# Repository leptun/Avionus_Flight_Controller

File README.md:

# Avionus_Flight_Controller

This repo contains the mainboard for the Avionus project, a semi-autonomous plane/drone. The project is work in progress 🚧.

Features:
- STM32F722ZE MCU with hardware float, 512KB of flash and 256KB of RAM
- 16MB total of external dual-mode QuadSPI (QPI) flash memory with XIP capability
- Full size SD card slot
- GPS (ublox MAX-M10S) with onboard antenna
- 9dof IMU ICM-20948
- LIDAR distance sensors with headers for:
  - LIDAR07-100W
  - VL53L1X
- 16 servo outputs (including at least one UART connection)
- RC remote input:
  - PPM interface
  - iBus interface
- LoRa 868MHz module using Semtech SX1262
- USB 2.0 FS with Type C connector (device only)
- Independent power domanins for the peripherals:
  - Power domains voltage measurement and monitoring
  - Current measurement of critical power domains
  - Very low power shutdown with wake from RTC
  - ESD protection of all IO
- STDC14 debugging header for STLINK-V3:
  - SWD
  - JTAG
  - SWO
  - UART

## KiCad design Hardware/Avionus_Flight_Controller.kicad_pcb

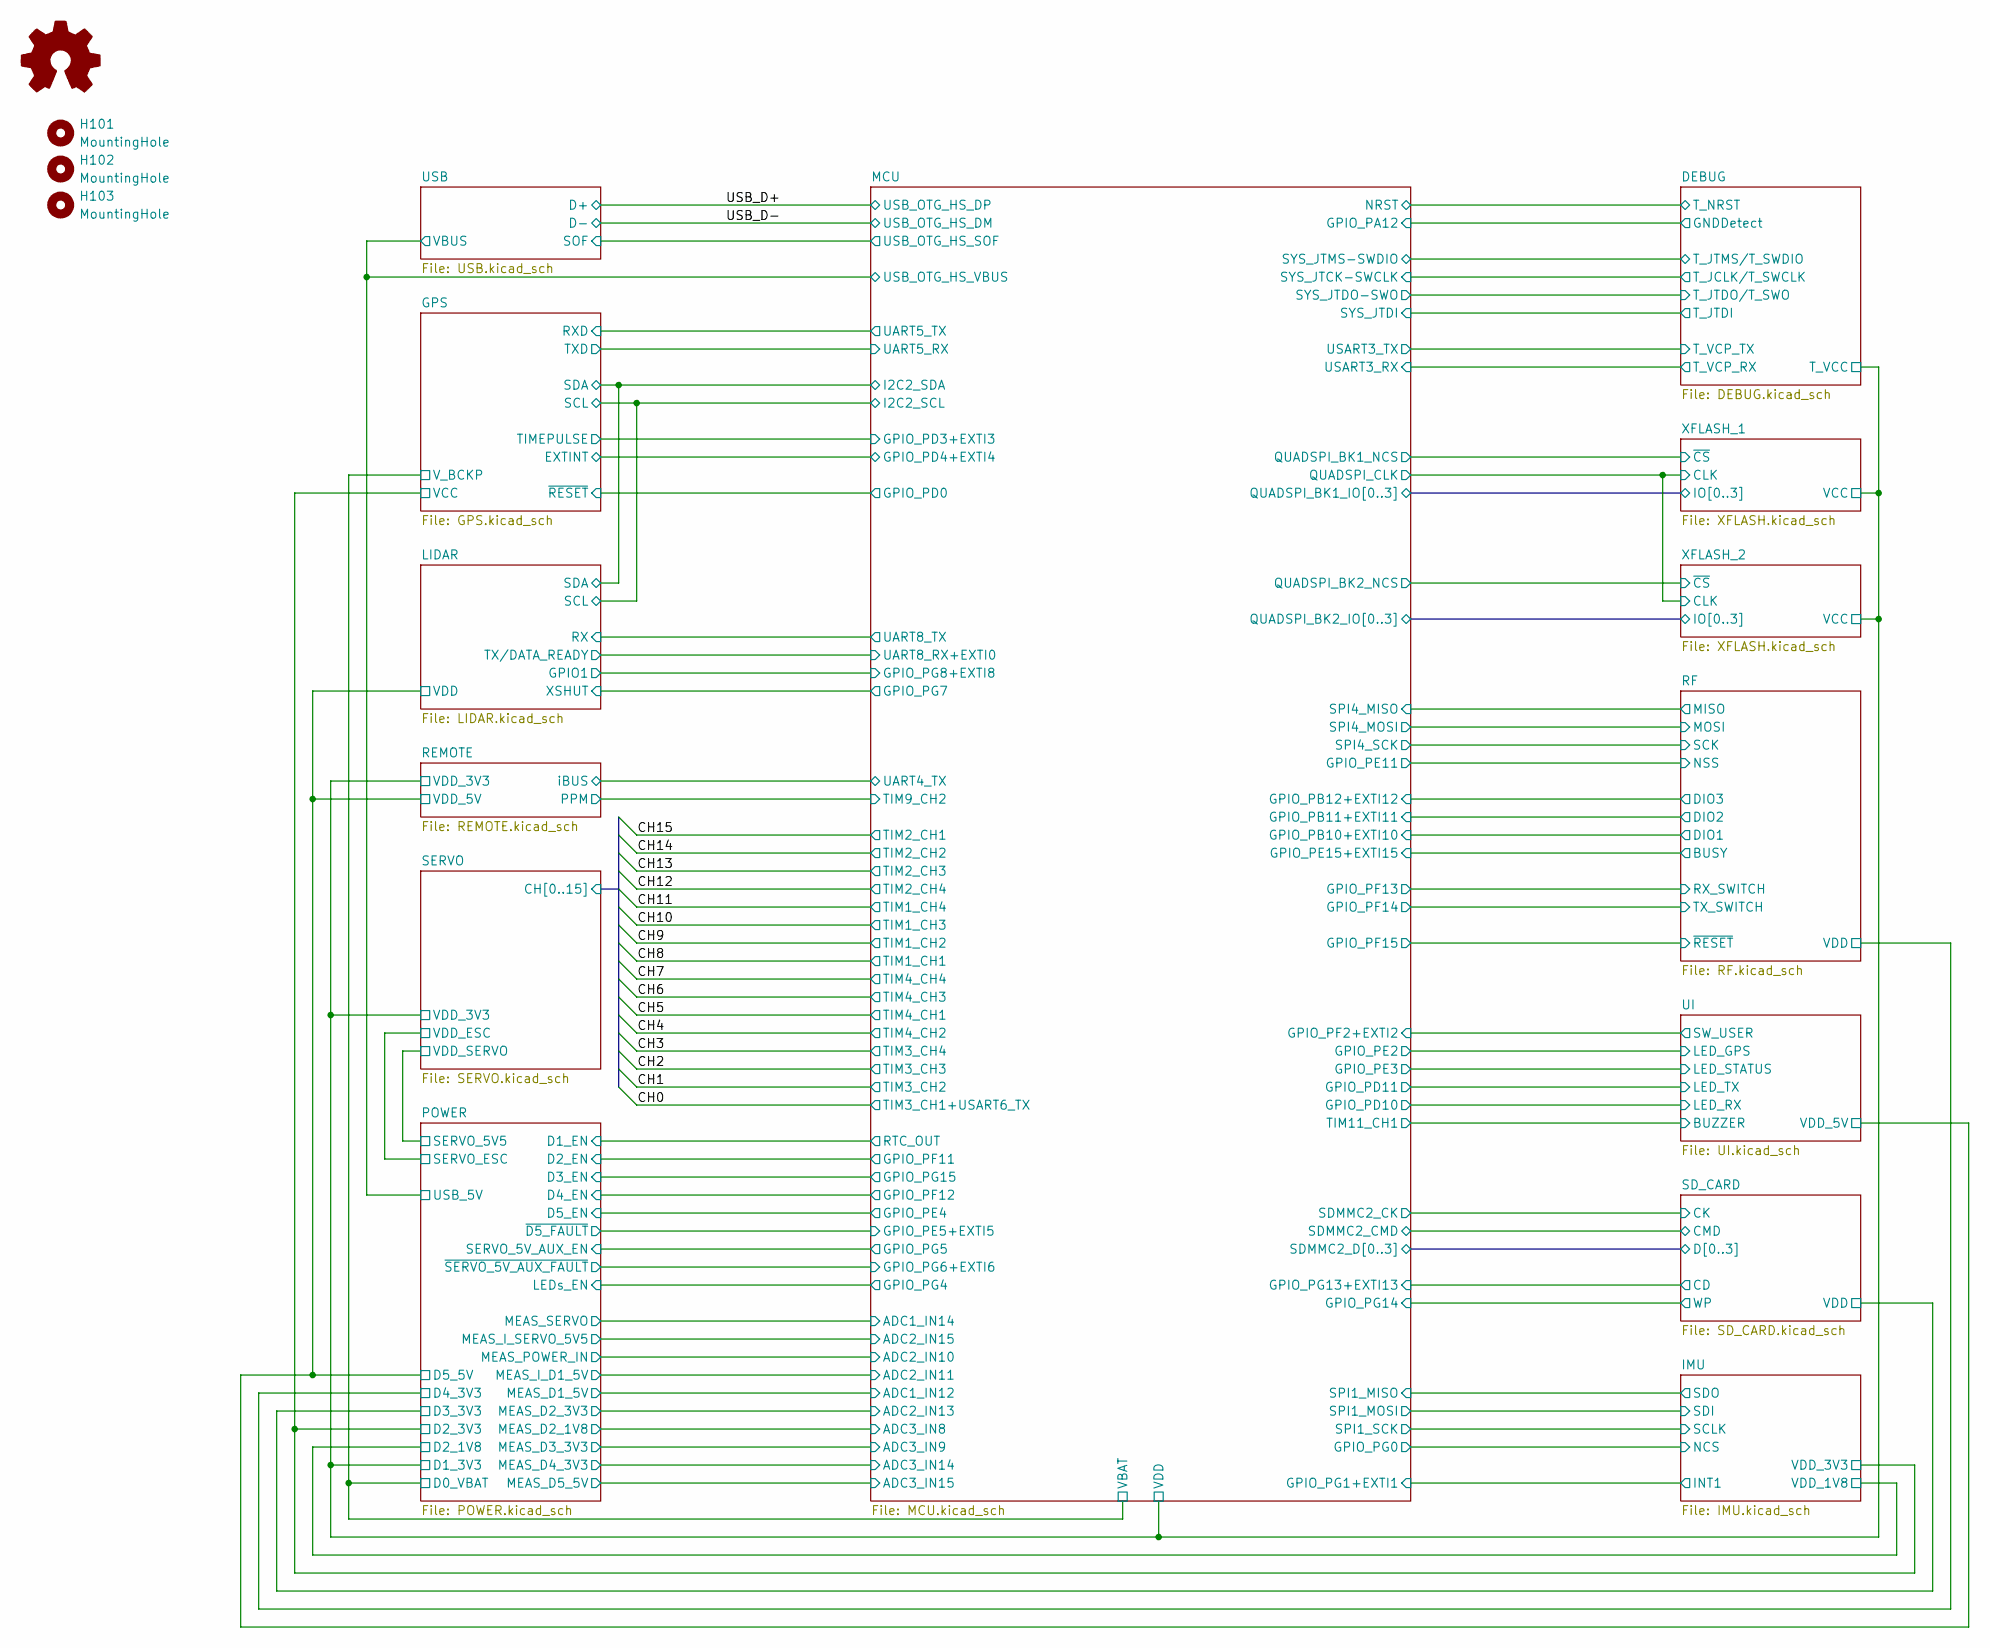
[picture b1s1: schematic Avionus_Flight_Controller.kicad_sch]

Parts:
H101, H102, H103: MountingHole; MountingHole_3.2mm_M3
SYM101: AMOGUS

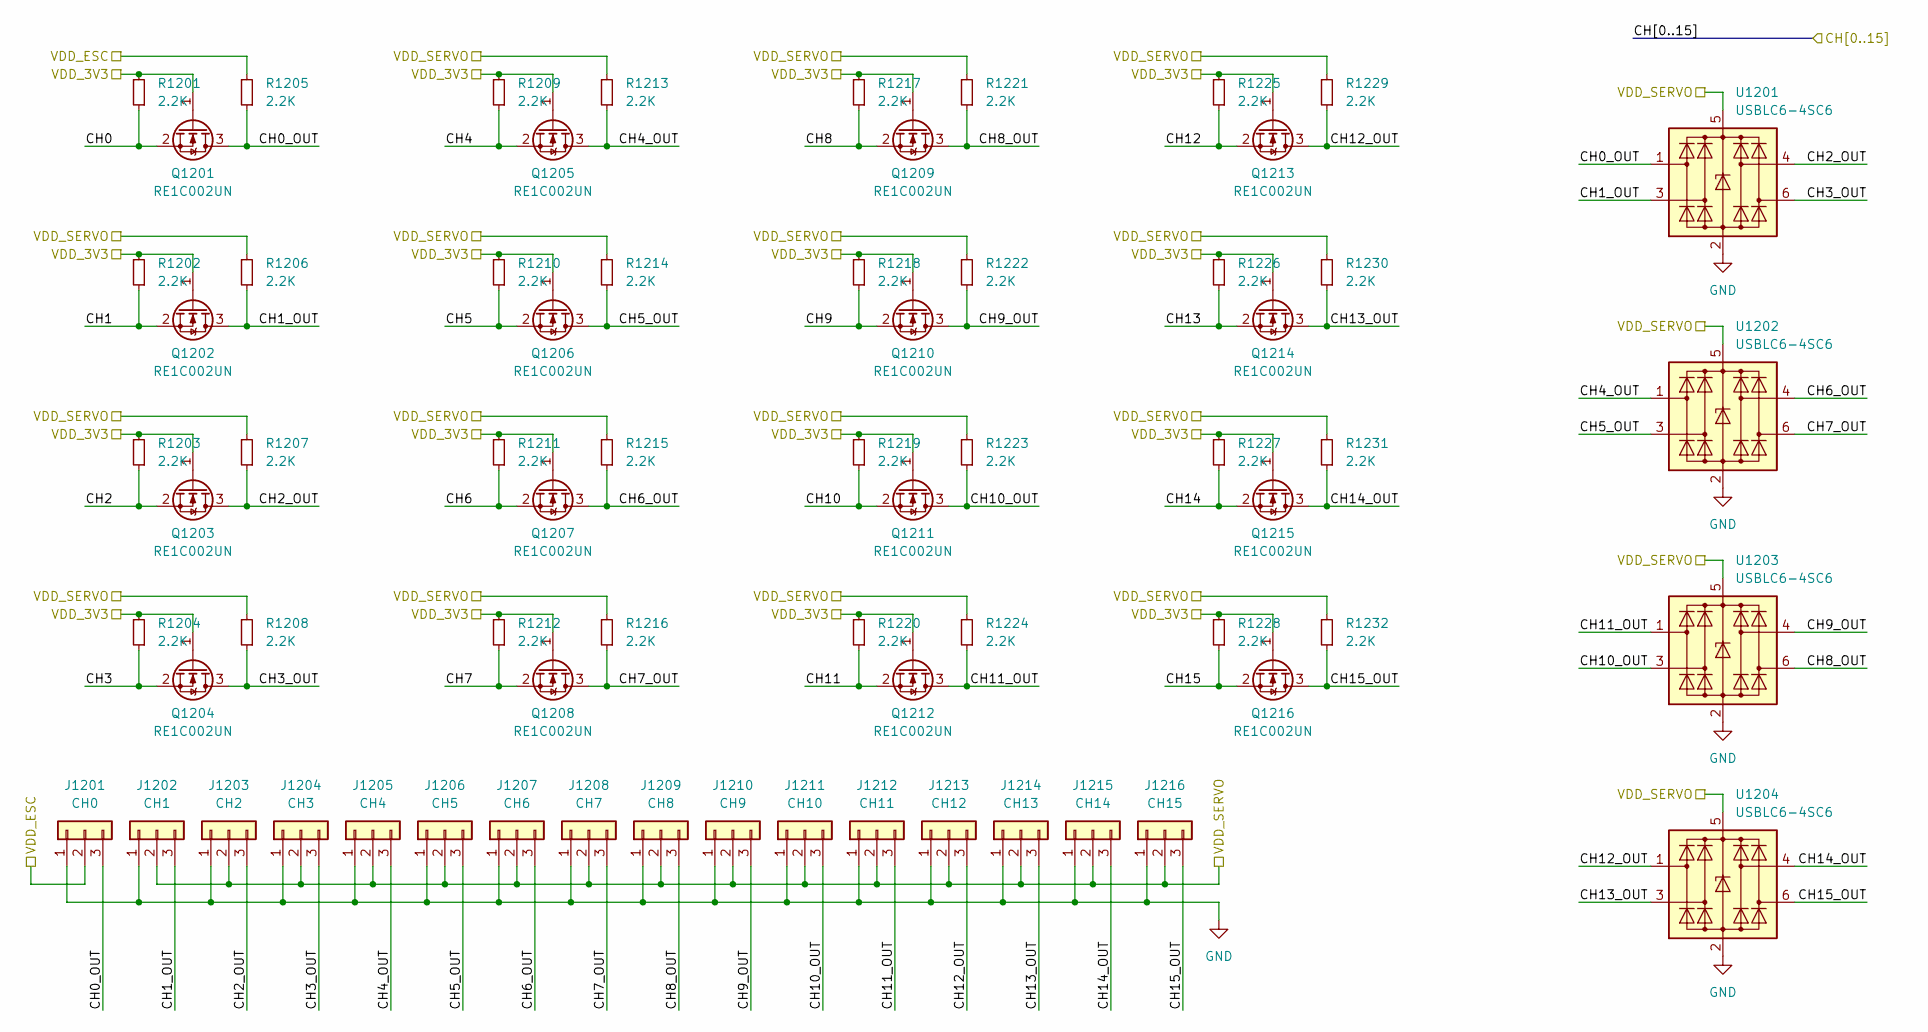
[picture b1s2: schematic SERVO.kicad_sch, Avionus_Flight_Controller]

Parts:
J1201: CH0; PinHeader_1x03_P2.54mm_Vertical
J1202: CH1; PinHeader_1x03_P2.54mm_Vertical
J1203: CH2; PinHeader_1x03_P2.54mm_Vertical
J1204: CH3; PinHeader_1x03_P2.54mm_Vertical
J1205: CH4; PinHeader_1x03_P2.54mm_Vertical
J1206: CH5; PinHeader_1x03_P2.54mm_Vertical
J1207: CH6; PinHeader_1x03_P2.54mm_Horizontal
J1208: CH7; PinHeader_1x03_P2.54mm_Horizontal
J1209: CH8; PinHeader_1x03_P2.54mm_Horizontal
J1210: CH9; PinHeader_1x03_P2.54mm_Horizontal
J1211: CH10; PinHeader_1x03_P2.54mm_Horizontal
J1212: CH11; PinHeader_1x03_P2.54mm_Horizontal
J1213: CH12; PinHeader_1x03_P2.54mm_Horizontal
J1214: CH13; PinHeader_1x03_P2.54mm_Horizontal
J1215: CH14; PinHeader_1x03_P2.54mm_Horizontal
J1216: CH15; PinHeader_1x03_P2.54mm_Horizontal
Q1201, Q1202, Q1203, Q1204, Q1205, Q1206, Q1207, Q1208, Q1209, Q1210, Q1211, Q1212, Q1213, Q1214, Q1215, Q1216: RE1C002UN; SOT-416
R1201, R1202, R1203, R1204, R1205, R1206, R1207, R1208, R1209, R1210, R1211, R1212, R1213, R1214, R1215, R1216, R1217, R1218, R1219, R1220, R1221, R1222, R1223, R1224, R1225, R1226, R1227, R1228, R1229, R1230, R1231, R1232: 2.2K; R_0805_2012Metric
U1201, U1202, U1203, U1204: USBLC6-4SC6; SOT-23-6

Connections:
/DEBUG/T_VCC: Q1201.1 (G), Q1202.1 (G), Q1203.1 (G), Q1204.1 (G), Q1205.1 (G), Q1206.1 (G), Q1207.1 (G), Q1208.1 (G), Q1209.1 (G), Q1210.1 (G), Q1211.1 (G), Q1212.1 (G), Q1213.1 (G), Q1214.1 (G), Q1215.1 (G), Q1216.1 (G), R1201.2, R1202.2, R1203.2, R1204.2, R1209.2, R1210.2, R1211.2, R1212.2, R1217.2, R1218.2, R1219.2, R1220.2, R1225.2, R1226.2, R1227.2, R1228.2; also elsewhere on the board
/POWER/SERVO_5V5: J1202.2, J1203.2, J1204.2, J1205.2, J1206.2, J1207.2, J1208.2, J1209.2, J1210.2, J1211.2, J1212.2, J1213.2, J1214.2, J1215.2, J1216.2, R1206.2, R1207.2, R1208.2, R1213.2, R1214.2, R1215.2, R1216.2, R1221.2, R1222.2, R1223.2, R1224.2, R1229.2, R1230.2, R1231.2, R1232.2, U1201.5 (VBUS), U1202.5 (VBUS), U1203.5 (VBUS), U1204.5 (VBUS); also elsewhere on the board
/POWER/SERVO_ESC: J1201.2, R1205.2; also elsewhere on the board
/SERVO/CH0: Q1201.2 (S), R1201.1; also elsewhere on the board
/SERVO/CH0_OUT: J1201.3, Q1201.3 (D), R1205.1, U1201.1 (I/O1)
/SERVO/CH1: Q1202.2 (S), R1202.1; also elsewhere on the board
/SERVO/CH1_OUT: J1202.3, Q1202.3 (D), R1206.1, U1201.3 (I/O2)
/SERVO/CH2: Q1203.2 (S), R1203.1; also elsewhere on the board
/SERVO/CH2_OUT: J1203.3, Q1203.3 (D), R1207.1, U1201.4 (I/O3)
/SERVO/CH3: Q1204.2 (S), R1204.1; also elsewhere on the board
/SERVO/CH3_OUT: J1204.3, Q1204.3 (D), R1208.1, U1201.6 (I/O4)
/SERVO/CH4: Q1205.2 (S), R1209.1; also elsewhere on the board
/SERVO/CH4_OUT: J1205.3, Q1205.3 (D), R1213.1, U1202.1 (I/O1)
/SERVO/CH5: Q1206.2 (S), R1210.1; also elsewhere on the board
/SERVO/CH5_OUT: J1206.3, Q1206.3 (D), R1214.1, U1202.3 (I/O2)
/SERVO/CH6: Q1207.2 (S), R1211.1; also elsewhere on the board
/SERVO/CH6_OUT: J1207.3, Q1207.3 (D), R1215.1, U1202.4 (I/O3)
/SERVO/CH7: Q1208.2 (S), R1212.1; also elsewhere on the board
/SERVO/CH7_OUT: J1208.3, Q1208.3 (D), R1216.1, U1202.6 (I/O4)
/SERVO/CH8: Q1209.2 (S), R1217.1; also elsewhere on the board
/SERVO/CH8_OUT: J1209.3, Q1209.3 (D), R1221.1, U1203.6 (I/O4)
/SERVO/CH9: Q1210.2 (S), R1218.1; also elsewhere on the board
/SERVO/CH9_OUT: J1210.3, Q1210.3 (D), R1222.1, U1203.4 (I/O3)
/SERVO/CH10: Q1211.2 (S), R1219.1; also elsewhere on the board
/SERVO/CH10_OUT: J1211.3, Q1211.3 (D), R1223.1, U1203.3 (I/O2)
/SERVO/CH11: Q1212.2 (S), R1220.1; also elsewhere on the board
/SERVO/CH11_OUT: J1212.3, Q1212.3 (D), R1224.1, U1203.1 (I/O1)
/SERVO/CH12: Q1213.2 (S), R1225.1; also elsewhere on the board
/SERVO/CH12_OUT: J1213.3, Q1213.3 (D), R1229.1, U1204.1 (I/O1)
/SERVO/CH13: Q1214.2 (S), R1226.1; also elsewhere on the board
/SERVO/CH13_OUT: J1214.3, Q1214.3 (D), R1230.1, U1204.3 (I/O2)
/SERVO/CH14: Q1215.2 (S), R1227.1; also elsewhere on the board
/SERVO/CH14_OUT: J1215.3, Q1215.3 (D), R1231.1, U1204.4 (I/O3)
/SERVO/CH15: Q1216.2 (S), R1228.1; also elsewhere on the board
/SERVO/CH15_OUT: J1216.3, Q1216.3 (D), R1232.1, U1204.6 (I/O4)
GND: J1201.1, J1202.1, J1203.1, J1204.1, J1205.1, J1206.1, J1207.1, J1208.1, J1209.1, J1210.1, J1211.1, J1212.1, J1213.1, J1214.1, J1215.1, J1216.1, U1201.2 (GND), U1202.2 (GND), U1203.2 (GND), U1204.2 (GND); also elsewhere on the board

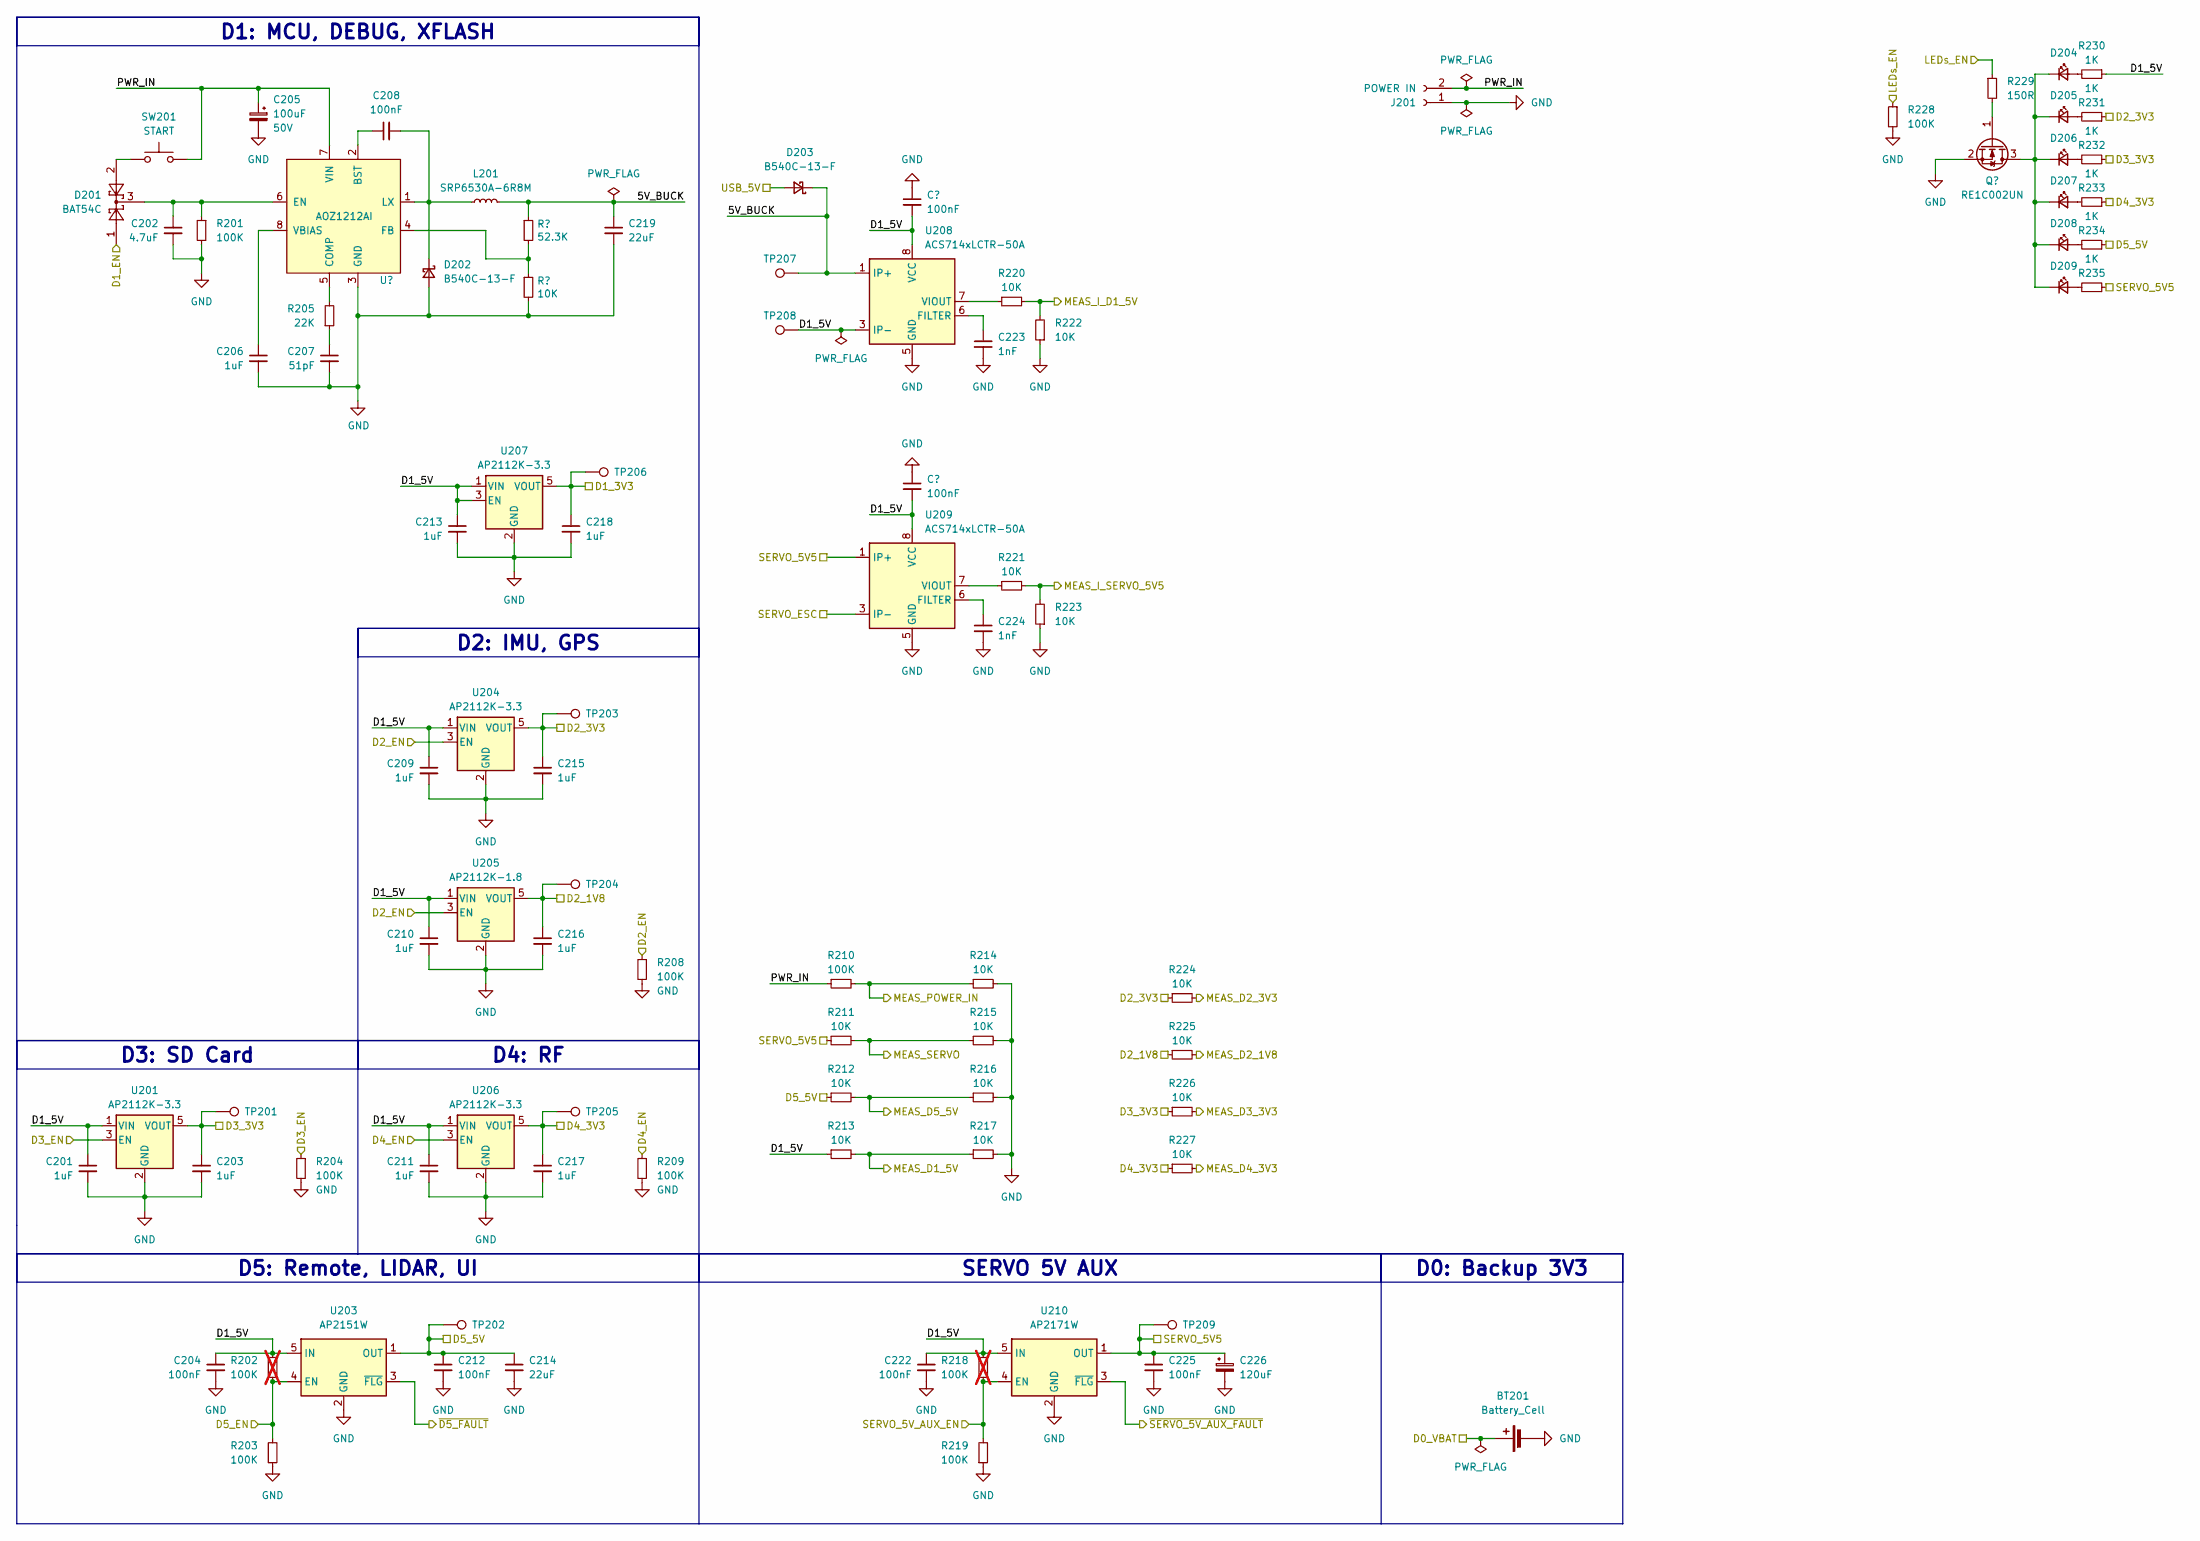
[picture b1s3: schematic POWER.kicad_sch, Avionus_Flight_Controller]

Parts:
BT201: Battery_Cell; DS1092-12-N8S
C201, C203, C206, C209, C210, C211, C213, C215, C216, C217, C218: 1uF; C_0805_2012Metric
C202: 4.7uF; C_1206_3216Metric
C204, C208, C212, C220, C221, C222, C225: 100nF; C_0603_1608Metric
C205: 100uF; C_Radial_D8.0mm_H11.5mm_P3.50mm; Rating 50V
C207: 51pF; C_0402_1005Metric
C214, C219: 22uF; C_1210_3225Metric
C223, C224: 1nF; C_0603_1608Metric
C226: 120uF; C_Radial_D6.3mm_H11.0mm_P2.50mm
D201: BAT54C; SOT-23
D202, D203: B540C-13-F; D_SMC
D204, D205, D206, D207, D208, D209: LED_1206_3216Metric
J201: POWER IN; AMASS_XT30UPB-M_1x02_P5.0mm_Vertical
L201: SRP6530A-6R8M
Q201: RE1C002UN; SOT-416
R201, R203, R204, R208, R209, R210, R219, R228: 100K; R_0805_2012Metric
R202, R218: 100K; R_0805_2012Metric; not fitted
R205: 22K; R_0805_2012Metric
R206: 52.3K; R_0603_1608Metric
R207, R211, R212, R213, R214, R215, R216, R217, R220, R221, R222, R223, R224, R225, R226, R227: 10K; R_0603_1608Metric
R229: 150R; R_0603_1608Metric
R230, R231, R232, R233, R234, R235: 1K; R_0805_2012Metric
SW201: START; SW_PUSH_6mm_H5mm
TP201, TP202, TP203, TP204, TP205, TP206, TP207, TP208, TP209: TestPoint_Pad_D1.0mm
U201, U204, U206, U207: AP2112K-3.3; SOT-23-5
U202: AOZ1212AI
U203: AP2151W; SOT-23-5
U205: AP2112K-1.8; SOT-23-5
U208, U209: ACS714xLCTR-50A; SOIC-8_3.9x4.9mm_P1.27mm
U210: AP2171W; SOT-23-5

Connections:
/DEBUG/T_VCC: C218.1, TP206.1, U207.5 (VOUT); also elsewhere on the board
/GPS/VCC: C215.1, R224.1, R231.1, TP203.1, U204.5 (VOUT); also elsewhere on the board
/GPS/V_BCKP: BT201.1 (+); also elsewhere on the board
/IMU/VDD_1V8: C216.1, R225.1, TP204.1, U205.5 (VOUT); also elsewhere on the board
/MCU/ADC1_IN12: R213.2, R217.1; also elsewhere on the board
/MCU/ADC1_IN14: R211.2, R215.1; also elsewhere on the board
/MCU/ADC2_IN10: R210.2, R214.1; also elsewhere on the board
/MCU/ADC2_IN11: R220.2, R222.2; also elsewhere on the board
/MCU/ADC2_IN13: R224.2; also elsewhere on the board
/MCU/ADC2_IN15: R221.2, R223.2; also elsewhere on the board
/MCU/ADC3_IN8: R225.2; also elsewhere on the board
/MCU/ADC3_IN9: R226.2; also elsewhere on the board
/MCU/ADC3_IN14: R227.2; also elsewhere on the board
/MCU/ADC3_IN15: R212.2, R216.1; also elsewhere on the board
/MCU/GPIO_PE4: R202.1, R203.2, U203.4 (EN); also elsewhere on the board
/MCU/GPIO_PE5+EXTI5: U203.3 (~FLG); also elsewhere on the board
/MCU/GPIO_PF11: R208.1, U204.3 (EN), U205.3 (EN); also elsewhere on the board
/MCU/GPIO_PF12: R209.1, U206.3 (EN); also elsewhere on the board
/MCU/GPIO_PG4: R228.1, R229.1; also elsewhere on the board
/MCU/GPIO_PG5: R218.1, R219.2, U210.4 (EN); also elsewhere on the board
/MCU/GPIO_PG6+EXTI6: U210.3 (~FLG); also elsewhere on the board
/MCU/GPIO_PG15: R204.1, U201.3 (EN); also elsewhere on the board
/MCU/RTC_OUT: D201.1; also elsewhere on the board
/POWER/5V_BUCK: C219.1, D203.1 (K), L201.2, R206.1, TP207.1, U208.1 (IP+), U208.2 (IP+)
/POWER/D1_5V: C201.1, C204.1, C209.1, C210.1, C211.1, C213.1, C220.2, C221.2, C222.1, R202.2, R213.1, R218.2, R230.1, TP208.1, U201.1 (VIN), U203.5 (IN), U204.1 (VIN), U205.1 (VIN), U206.1 (VIN), U207.1 (VIN), U207.3 (EN), U208.3 (IP-), U208.4 (IP-), U208.8 (VCC), U209.8 (VCC), U210.5 (IN)
/POWER/D3_3V3: C203.1, R226.1, R232.1, TP201.1, U201.5 (VOUT); also elsewhere on the board
/POWER/D4_3V3: C217.1, R227.1, R233.1, TP205.1, U206.5 (VOUT); also elsewhere on the board
/POWER/PWR_IN: C205.1, J201.2, R210.1, SW201.2, U202.7 (VIN)
/POWER/SERVO_5V5: C225.1, C226.1, R211.1, R235.1, TP209.1, U209.1 (IP+), U209.2 (IP+), U210.1 (OUT); also elsewhere on the board
/POWER/SERVO_ESC: U209.3 (IP-), U209.4 (IP-); also elsewhere on the board
GND: BT201.2 (-), C201.2, C202.2, C203.2, C204.2, C205.2, C206.2, C207.2, C209.2, C210.2, C211.2, C212.2, C213.2, C214.2, C215.2, C216.2, C217.2, C218.2, C219.2, C220.1, C221.1, C222.2, C223.2, C224.2, C225.2, C226.2, D202.2 (A), J201.1, Q201.2 (S), R201.2, R203.1, R204.2, R207.2, R208.2, R209.2, R214.2, R215.2, R216.2, R217.2, R219.1, R222.1, R223.1, R228.2, U201.2 (GND), U202.3 (GND), U203.2 (GND), U204.2 (GND), U205.2 (GND), U206.2 (GND), U207.2 (GND), U208.5 (GND), U209.5 (GND), U210.2 (GND); also elsewhere on the board
unnamed: C207.1, R205.1
unnamed: D201.2, SW201.1
unnamed: C208.2, D202.1 (K), L201.1, U202.1 (LX)
unnamed: D204.2 (A), R230.2
unnamed: D204.1 (K), D205.1 (K), D206.1 (K), D207.1 (K), D208.1 (K), D209.1 (K), Q201.3 (D)
unnamed: D205.2 (A), R231.2
unnamed: D206.2 (A), R232.2
unnamed: D207.2 (A), R233.2
unnamed: D208.2 (A), R234.2
unnamed: D209.2 (A), R235.2
unnamed: Q201.1 (G), R229.2
unnamed: C208.1, U202.2 (BST)
unnamed: R205.2, U202.5 (COMP)
unnamed: C202.1, D201.3, R201.1, U202.6 (EN)
unnamed: R206.2, R207.1, U202.4 (FB)
unnamed: C206.1, U202.8 (VBIAS)
unnamed: C223.1, U208.6 (FILTER)
unnamed: R220.1, U208.7 (VIOUT)
unnamed: C224.1, U209.6 (FILTER)
unnamed: R221.1, U209.7 (VIOUT)

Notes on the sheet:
D5: Remote, LIDAR, UI
SERVO 5V AUX
D0: Backup 3V3
D3: SD Card
D4: RF
D1: MCU, DEBUG, XFLASH
D2: IMU, GPS

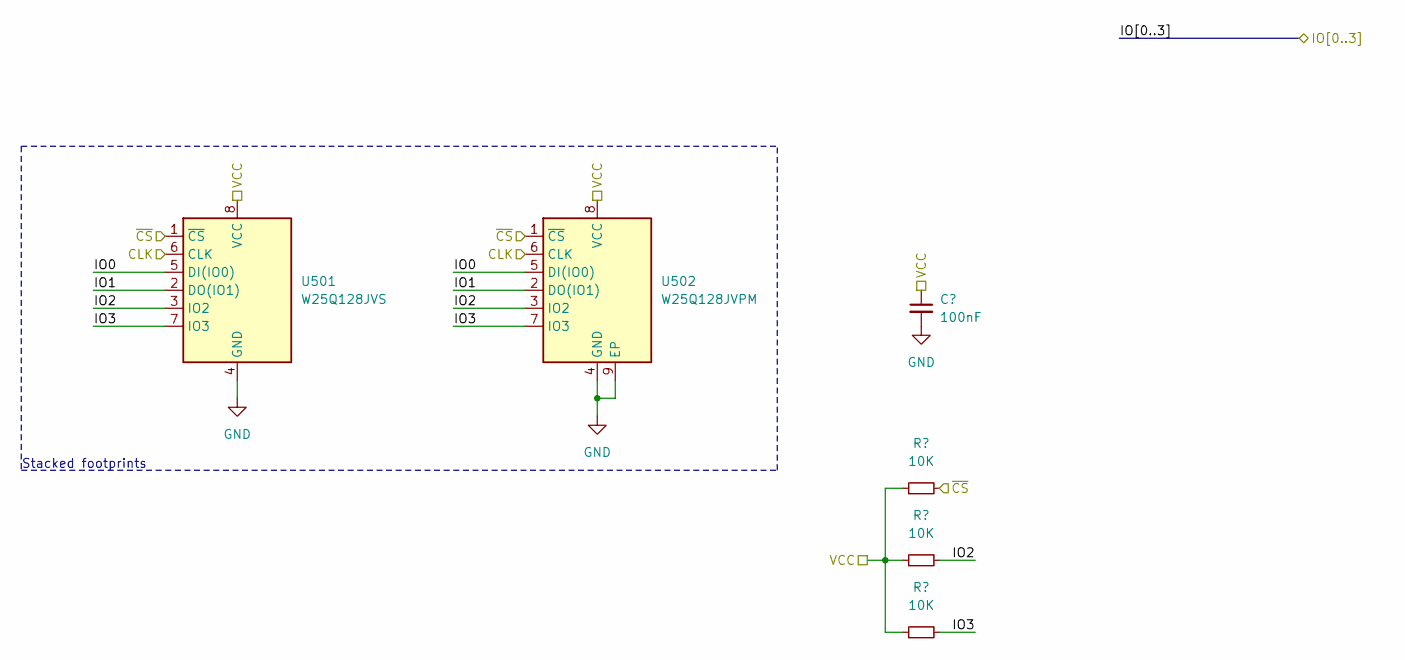
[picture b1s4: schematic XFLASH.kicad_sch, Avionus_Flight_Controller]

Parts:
C501: 100nF; C_0603_1608Metric
R501, R502, R503: 10K; R_0603_1608Metric
U501: W25Q128JVS; SOIC-8_5.23x5.23mm_P1.27mm
U502: W25Q128JVPM; WSON-8-1EP_6x5mm_P1.27mm_EP3.4x4.3mm

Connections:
/DEBUG/T_VCC: C501.1, R501.1, R502.1, R503.1, U501.8 (VCC), U502.8 (VCC); also elsewhere on the board
/MCU/QUADSPI_BK1_IO0: U501.5 (DI(IO0)), U502.5 (DI(IO0)); also elsewhere on the board
/MCU/QUADSPI_BK1_IO1: U501.2 (DO(IO1)), U502.2 (DO(IO1)); also elsewhere on the board
/MCU/QUADSPI_BK1_IO2: R502.2, U501.3 (IO2), U502.3 (IO2); also elsewhere on the board
/MCU/QUADSPI_BK1_IO3: R503.2, U501.7 (IO3), U502.7 (IO3); also elsewhere on the board
/MCU/QUADSPI_BK1_NCS: R501.2, U501.1 (~CS), U502.1 (~CS); also elsewhere on the board
/MCU/QUADSPI_CLK: U501.6 (CLK), U502.6 (CLK); also elsewhere on the board
GND: C501.2, U501.4 (GND), U502.4 (GND), U502.9 (EP); also elsewhere on the board

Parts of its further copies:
C601: 100nF; C_0603_1608Metric
R601, R602, R603: 10K; R_0603_1608Metric
U601: W25Q128JVS; SOIC-8_5.23x5.23mm_P1.27mm
U602: W25Q128JVPM; WSON-8-1EP_6x5mm_P1.27mm_EP3.4x4.3mm

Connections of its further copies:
/DEBUG/T_VCC: C601.1, R601.1, R602.1, R603.1, U601.8 (VCC), U602.8 (VCC); also elsewhere on the board
/MCU/QUADSPI_BK2_IO0: U601.5 (DI(IO0)), U602.5 (DI(IO0)); also elsewhere on the board
/MCU/QUADSPI_BK2_IO1: U601.2 (DO(IO1)), U602.2 (DO(IO1)); also elsewhere on the board
/MCU/QUADSPI_BK2_IO2: R602.2, U601.3 (IO2), U602.3 (IO2); also elsewhere on the board
/MCU/QUADSPI_BK2_IO3: R603.2, U601.7 (IO3), U602.7 (IO3); also elsewhere on the board
/MCU/QUADSPI_BK2_NCS: R601.2, U601.1 (~CS), U602.1 (~CS); also elsewhere on the board
/MCU/QUADSPI_CLK: U601.6 (CLK), U602.6 (CLK); also elsewhere on the board
GND: C601.2, U601.4 (GND), U602.4 (GND), U602.9 (EP); also elsewhere on the board

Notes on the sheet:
Stacked footprints

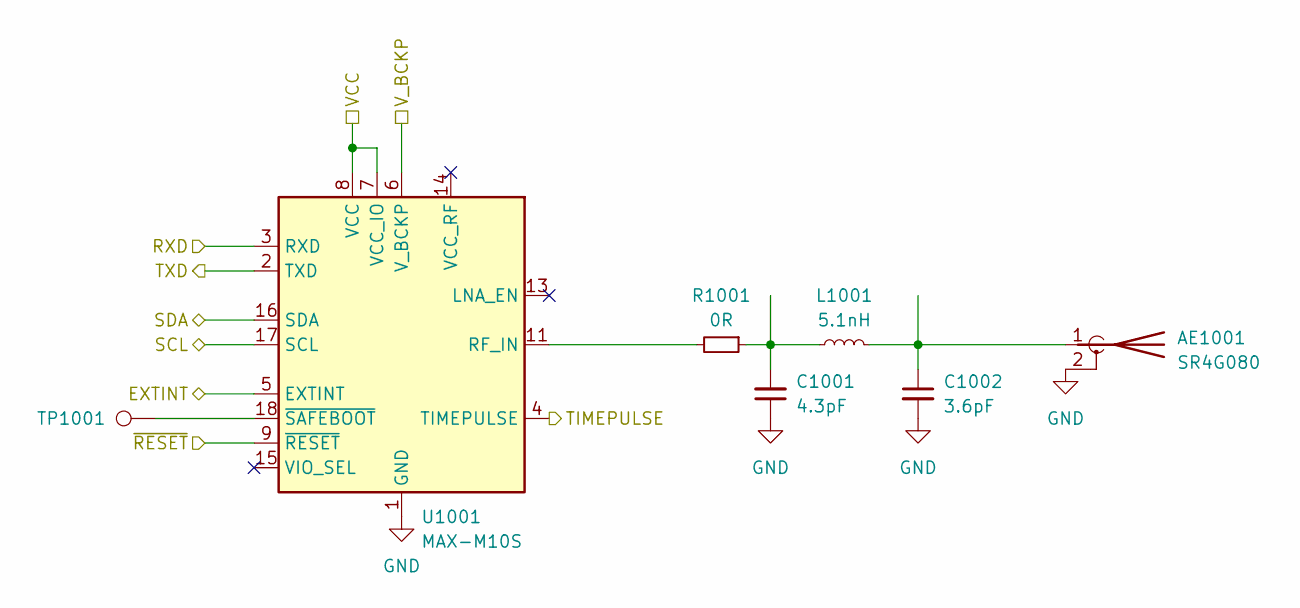
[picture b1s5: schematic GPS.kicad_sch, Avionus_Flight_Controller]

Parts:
AE1001: SR4G080
C1001: 4.3pF; C_0402_1005Metric_Pad0.74x0.62mm_HandSolder
C1002: 3.6pF; C_0402_1005Metric_Pad0.74x0.62mm_HandSolder
L1001: 5.1nH; L_0402_1005Metric_Pad0.77x0.64mm_HandSolder
R1001: 0R; R_0402_1005Metric_Pad0.72x0.64mm_HandSolder
TP1001: TestPoint_Pad_D1.0mm
U1001: MAX-M10S; ublox_MAX

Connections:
/GPS/EXTINT: U1001.5 (EXTINT); also elsewhere on the board
/GPS/RXD: U1001.3 (RXD); also elsewhere on the board
/GPS/SCL: U1001.17 (SCL); also elsewhere on the board
/GPS/SDA: U1001.16 (SDA); also elsewhere on the board
/GPS/TIMEPULSE: U1001.4 (TIMEPULSE); also elsewhere on the board
/GPS/TXD: U1001.2 (TXD); also elsewhere on the board
/GPS/VCC: U1001.7 (VCC_IO), U1001.8 (VCC); also elsewhere on the board
/GPS/V_BCKP: U1001.6 (V_BCKP); also elsewhere on the board
/GPS/~RESET: U1001.9 (~RESET); also elsewhere on the board
GND: AE1001.2 (Shield), C1001.1, C1002.2, U1001.1 (GND), U1001.10 (GND), U1001.12 (GND); also elsewhere on the board
unnamed: AE1001.1 (A), C1002.1, L1001.2
unnamed: C1001.2, L1001.1, R1001.1
unnamed: R1001.2, U1001.11 (RF_IN)
unnamed: TP1001.1, U1001.18 (~SAFEBOOT)

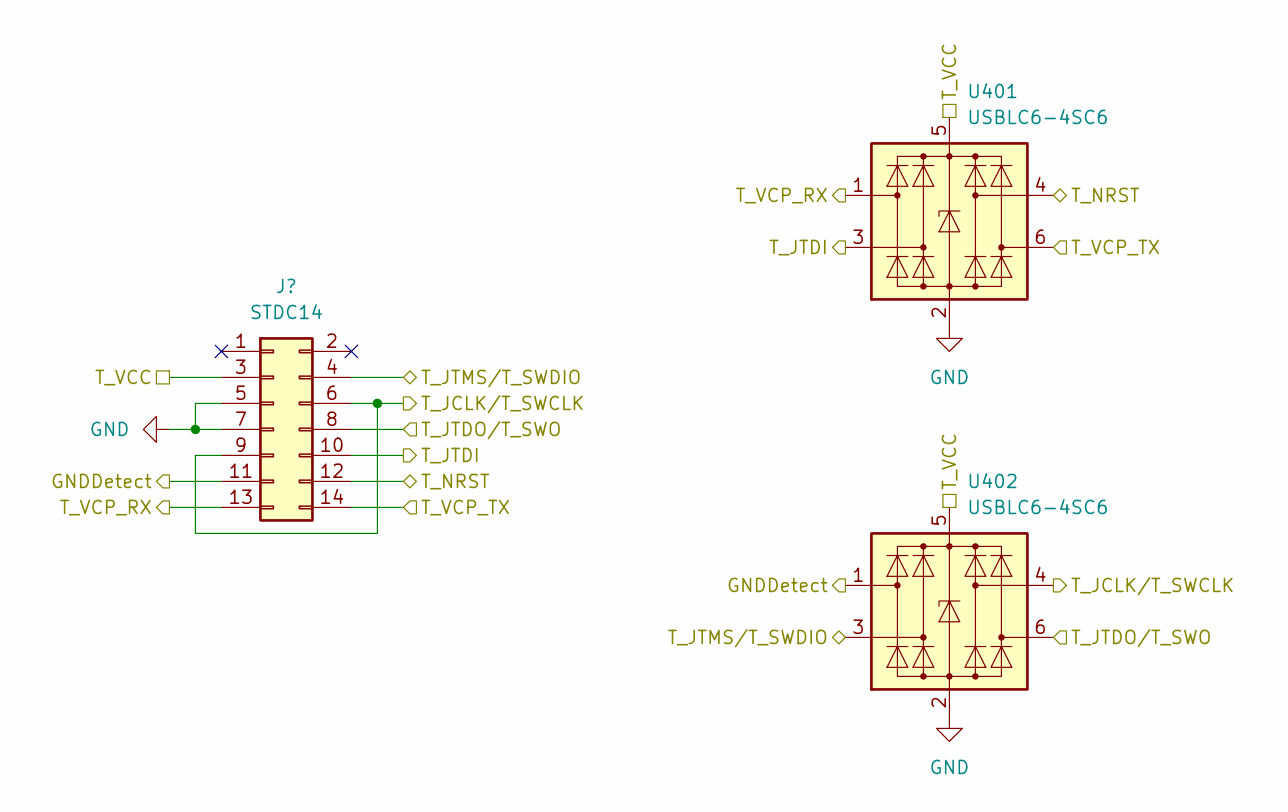
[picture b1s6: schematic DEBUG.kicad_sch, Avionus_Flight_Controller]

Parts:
J401: STDC14; FTSH-107-01-L-DV-K-A
U401, U402: USBLC6-4SC6; SOT-23-6

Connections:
/DEBUG/GNDDetect: J401.11, U402.1 (I/O1); also elsewhere on the board
/DEBUG/T_JCLK/T_SWCLK: J401.6, J401.9, U402.4 (I/O3); also elsewhere on the board
/DEBUG/T_JTDI: J401.10, U401.3 (I/O2); also elsewhere on the board
/DEBUG/T_JTDO/T_SWO: J401.8, U402.6 (I/O4); also elsewhere on the board
/DEBUG/T_JTMS/T_SWDIO: J401.4, U402.3 (I/O2); also elsewhere on the board
/DEBUG/T_NRST: J401.12, U401.4 (I/O3); also elsewhere on the board
/DEBUG/T_VCC: J401.3, U401.5 (VBUS), U402.5 (VBUS); also elsewhere on the board
/DEBUG/T_VCP_RX: J401.13, U401.1 (I/O1); also elsewhere on the board
/DEBUG/T_VCP_TX: J401.14, U401.6 (I/O4); also elsewhere on the board
GND: J401.5, J401.7, U401.2 (GND), U402.2 (GND); also elsewhere on the board

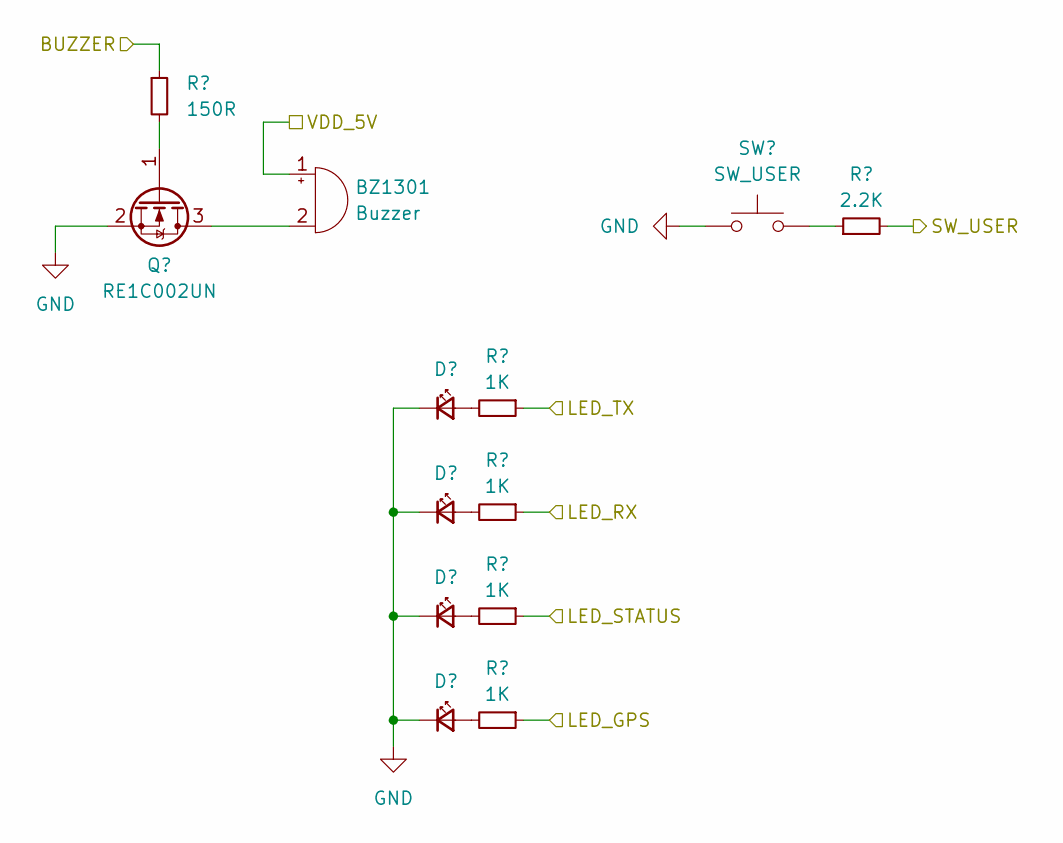
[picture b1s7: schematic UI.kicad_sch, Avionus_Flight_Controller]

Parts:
BZ1301: Buzzer; Buzzer_12x9.5RM7.6
D1301, D1302, D1303, D1304: LED_1206_3216Metric
Q1301: RE1C002UN; SOT-416
R1301: 150R; R_0603_1608Metric
R1302, R1303, R1304, R1305: 1K; R_0805_2012Metric
R1306: 2.2K; R_0805_2012Metric
SW1301: SW_USER; SW_PUSH_6mm_H5mm

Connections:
/MCU/GPIO_PD10: R1303.1; also elsewhere on the board
/MCU/GPIO_PD11: R1302.1; also elsewhere on the board
/MCU/GPIO_PE2: R1305.1; also elsewhere on the board
/MCU/GPIO_PE3: R1304.1; also elsewhere on the board
/MCU/GPIO_PF2+EXTI2: R1306.2; also elsewhere on the board
/MCU/TIM11_CH1: R1301.1; also elsewhere on the board
GND: D1301.1 (K), D1302.1 (K), D1303.1 (K), D1304.1 (K), Q1301.2 (S), SW1301.1; also elsewhere on the board
unnamed: BZ1301.2 (+), Q1301.3 (D)
unnamed: D1301.2 (A), R1302.2
unnamed: D1302.2 (A), R1303.2
unnamed: D1303.2 (A), R1304.2
unnamed: D1304.2 (A), R1305.2
unnamed: Q1301.1 (G), R1301.2
unnamed: R1306.1, SW1301.2
